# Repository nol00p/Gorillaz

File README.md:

# Gorillaz PCB Boards

This project offers an integrated PCB replacement for the Kinesys Advantage2. The view of this project is to offer a full PCB replacement including the thumb clusters.
The PCB components are almost fully SMD. The Draw back will be the cost of the solution on order, but the benefit will be solderless solution. 

### How is it different from other mods

Aside from being a fun project the main goal of this is to offer a simplified approach to Kinesys moddiing. 
- solder free installation (as much as possible)
- battery management with the ability to wake the board up from sleep by pressing a key (not possible with the nice!nano)
- Bluetooth

If there are feature you would like to see supported on the board, do get in touch. 
note that I am not planning on supporting the pedals at this stage.

### The Hardware

### The Software
the firmware will be ZMK. 

## Attribution
This project would not be possible without the huge work done by 
https://github.com/dcpedit/pillzmod

The pcb design wouldn't have been possible withouth the guide from Moritz ebastler - https://github.com/ebastler/zmk-designguide

## Contribustions 
I am no pcb designer so I am very much looking for contributions and feedback to get the project to the finish line. 

## Current design
### Schema

### pcb

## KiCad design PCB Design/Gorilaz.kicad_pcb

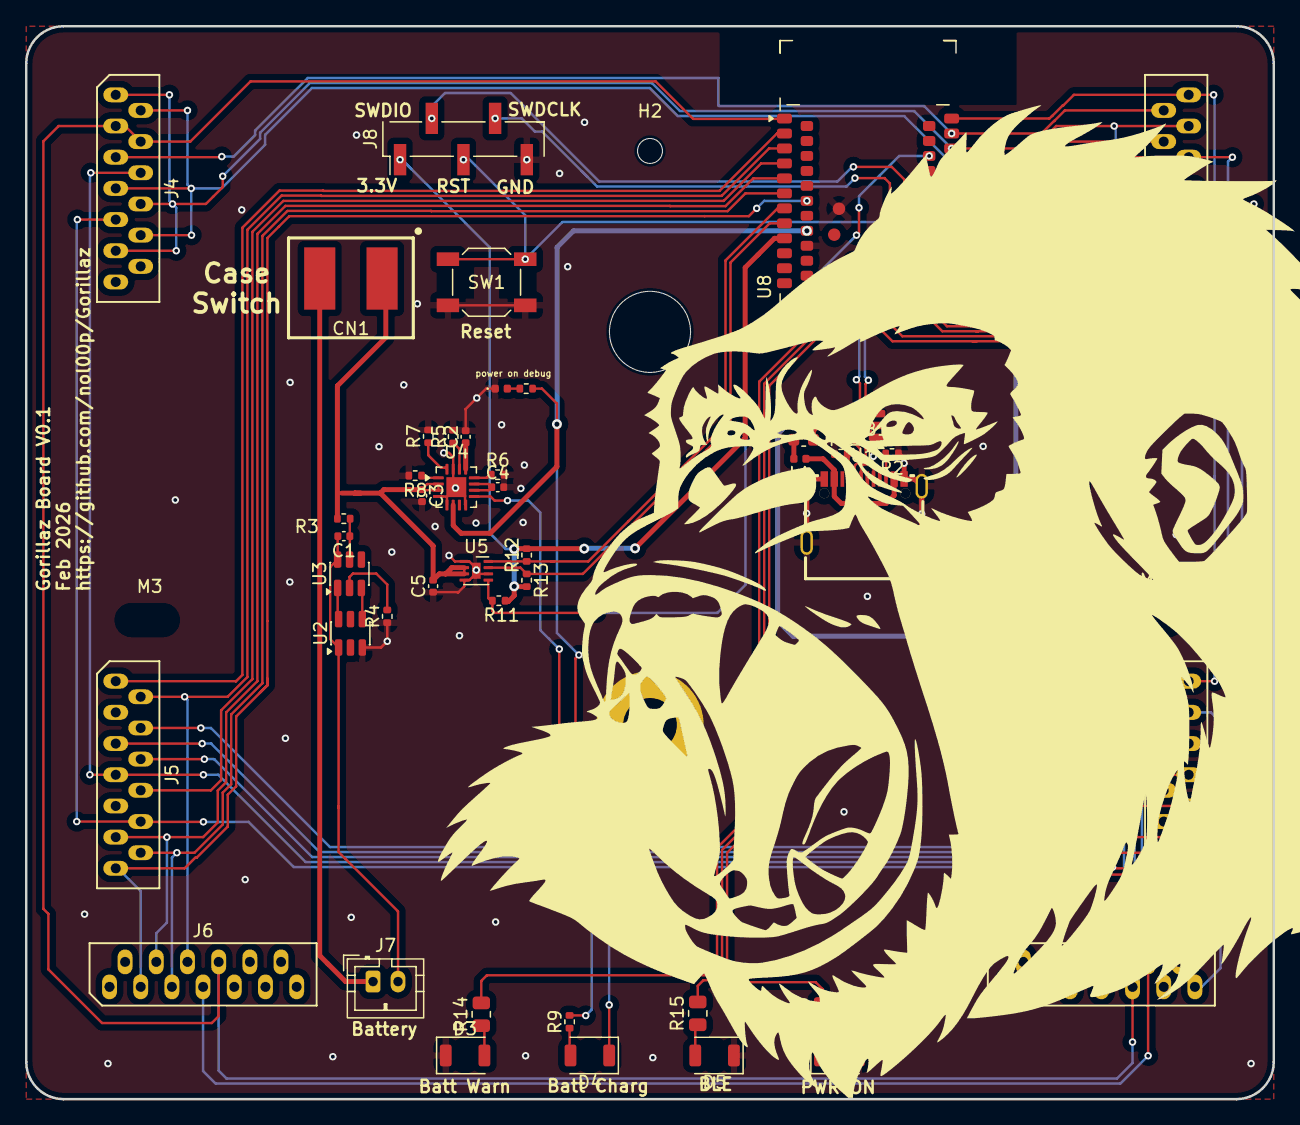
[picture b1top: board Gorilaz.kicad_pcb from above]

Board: 2 copper layers, 100.0 x 86.0 mm, 50 parts (0 on the bottom side), 58 nets.

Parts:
C1, C5: 100n; C_0402_1005Metric
C2, C3, C4: 4u7; C_0402_1005Metric
CN1: 950-D-SMD-DS/02; CONN-SMD_2P-P5.00_950-D-SMD-DS-02
D1: LED_PWON; LED_1206_3216Metric_ReverseMount_Hole1.8x2.4mm
D2: pwr ON; LED_0402_1005Metric
D3: LED_BATT_WARN; LED_1206_3216Metric_ReverseMount_Hole1.8x2.4mm
D4: LED_CHARGING; LED_1206_3216Metric_ReverseMount_Hole1.8x2.4mm
D5: LED_BLE; LED_1206_3216Metric_ReverseMount_Hole1.8x2.4mm
F1: 750 mA; Fuse_0603_1608Metric
H1: mounting pad; MountingHole_4.3mm_M4_Pad
H2: mounting pad; MountingHole_2mm
J1, J2, J3, J4, J5, J6: Conn_01x13; Molex_0039532135
J7: Battery; JST_PH_B2B-PH-K_1x02_P2.00mm_Vertical
J8: Conn_01x05_MountingPin; PinHeader_1x05_P2.54mm_Vertical_SMD_Pin1Left
L1: BLM15PX121SN1D; L_0402_1005Metric
M1: MountingHole_6.4mm_M6
M3, M4: MountingHole_4.3mm_M4
R1, R2, R11, R12, R13: 5k1; R_0402_1005Metric
R3: 100R; R_0402_1005Metric
R4, R10: 1k; R_0402_1005Metric
R5: 47k; R_0402_1005Metric
R6, R9: 1k5; R_0402_1005Metric
R7: 3k9; R_0402_1005Metric
R8: 10k; R_0402_1005Metric
R14, R15, R16: 10k; R_0805_2012Metric
SW1: RST; SW_SPST_SKQG_WithStem
U1: SRV05-4; SOT-23-6
U2: FS8205; SOT-23-6
U3: DW01A; SOT-23-6
U4: BQ24075; VQFN-16-1EP_3x3mm_P0.5mm_EP1.6x1.6mm
U5: MAX17048; DFN-8-1EP_2x2mm_P0.5mm_EP0.7x1.3mm
U8: nRF52840_moko_mk08
USB1: USB-310M-B-SU; USB-C-SMD_USB-310M-B-SU

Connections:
+3.3V: J8.1, R11.2, R12.2, R13.2, U8.9 (VDD)
+5V: C2.1, F1.2, U1.5 (VP), U4.13 (IN), U8.46 (VBUS)
+BATT: C3.1, C5.2, CN1.2, R3.1, U4.2 (BAT), U4.3 (BAT), U5.2 (CELL), U5.3 (VDD)
+VSW: C4.1, D4.1 (K), R10.2, U4.6 (EN1), U4.10 (OUT), U4.11 (OUT), U8.42 (VDDH)
/ILIM: R6.1, U4.12 (ILIM)
/TMR: R5.1, U4.14 (TMR)
ALERT: R11.1, U5.5 (~ALRT), U8.54 (P1.05-LF)
GND: C2.2, C3.2, C4.2, C5.1, D1.2 (A), D2.1 (K), D3.1 (K), D5.1 (K), H1.1, J8.5, R1.1, R2.1, R4.1, R5.2, R6.2, R7.2, R8.2, SW1.2, U1.2 (VN), U2.3 (S2), U4.4 (~CE), U4.5 (EN2), U4.8 (VSS), U4.15 (SYSOFF), U4.17 (VSS), U5.1 (CTG), U5.4 (GND), U5.6 (QSTRT), U5.9 (GND), U8.10 (GND), U8.39 (GND), U8.43 (GND), U8.57 (GND), USB1.1 (SHELL), USB1.2 (SHELL), USB1.3 (SHELL), USB1.4 (SHELL), USB1.A1B12 (GND), USB1.B1A12 (GND)
LED_BATT_WARN: R14.2, U8.13 (P0.04-A)
LED_BLE: R15.2, U8.14 (P0.06)
LED_POWER_ON: R16.2, U8.15 (P0.11)
unnamed: D1.1 (K), R16.1
unnamed: D2.2 (A), R10.1
unnamed: D3.2 (A), R14.1
unnamed: D4.2 (A), R9.1
unnamed: D5.2 (A), R15.1
unnamed: F1.1, L1.2
unnamed: CN1.1, J7.1
unnamed: C1.2, J7.2, U2.1 (S1), U3.6 (VSS)
unnamed: U2.6 (G1), U3.1 (OD)
unnamed: U2.4 (G2), U3.3 (OC)
unnamed: R4.2, U3.2 (CSI)
unnamed: C1.1, R3.2, U3.5 (VDD)
unnamed: R7.1, U4.16 (ISET)
unnamed: R8.1, U4.1 (TS)
unnamed: R9.2, U4.9 (~CHG)
unnamed: R1.2, USB1.A5 (CC1)
unnamed: R2.2, USB1.B5 (CC2)
RST: J8.3, SW1.1, U8.27 (P0.18-RESET)
SCL: R13.1, U5.7 (SCL), U8.8 (P0.05-A)
SDA: R12.1, U5.8 (SDA), U8.7 (P0.07)
SWDCLK: J8.4, U8.19 (SWDCLK)
SWDIO: J8.2, U8.20 (SWDIO)
USB-D+: U8.48 (USB-D+), USB1.A6 (DP1), USB1.B6 (DP2)
USB-D-: U8.47 (USB-D-), USB1.A7 (DN1), USB1.B7 (DN2)
VBUS: L1.1, USB1.B4A9 (VBUS)
col0: J1.13, J2.13, J5.4, U8.34 (P0.25)
col1: J1.6, J2.5, J5.5, U8.29 (P0.20)
col2: J1.9, J2.3, J5.6, U8.30 (P0.21)
col3: J2.2, J4.6, J5.7, U8.21 (P0.12)
col4: J2.1, J4.9, J5.10, U8.18 (P0.10-LF-NFC)
col5: J3.9, J4.3, J4.4, J6.8, U8.1 (P0.03-LF-A)
col6: J3.10, J6.7, U8.17 (P0.09-LF-NFC)
row0: J2.6, U8.22 (P0.13)
row1: J2.7, U8.23 (P0.14)
row2: J2.8, J3.12, U8.24 (P0.15)
row3: J2.10, J3.6, U8.25 (P0.16)
row4: J2.11, J3.13, U8.26 (P0.17)
row5: J2.12, J3.11, U8.28 (P0.19)
row6: J5.13, J6.3, U8.40 (P1.14-LF)
row7: J5.11, J6.4, U8.5 (P0.30-LF-A)
row8: J5.12, J6.5, U8.6 (P0.31-LF-A)
row9: J5.2, J6.6, U8.3 (P0.28-LF-A)
row10: J5.1, U8.2 (P0.02-LF-A)
row11: J5.8, U8.4 (P0.29-LF-A)
row12: J1.12, J4.5, U8.33 (P0.24)
row13: J1.4, J1.8, J1.11, J4.1, J4.8, J4.11, U8.32 (P0.23)
row14: J1.3, J1.7, J1.10, J4.2, J4.7, J4.10, U8.31 (P0.22)

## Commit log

2026-01-27 LED package
2026-01-29 schema update
2026-01-31 Data lane correction
2026-01-31 USB-C update
2026-02-02 power managemnt rework
2026-02-04 big updates push
2026-02-04 cleanup
2026-02-06 render update
2026-02-09 update pre-prod
2026-02-11 ESD update
2026-02-12 lots of improvement
2026-02-12 clean up
2026-02-12 readme update
2026-02-13 LED update
